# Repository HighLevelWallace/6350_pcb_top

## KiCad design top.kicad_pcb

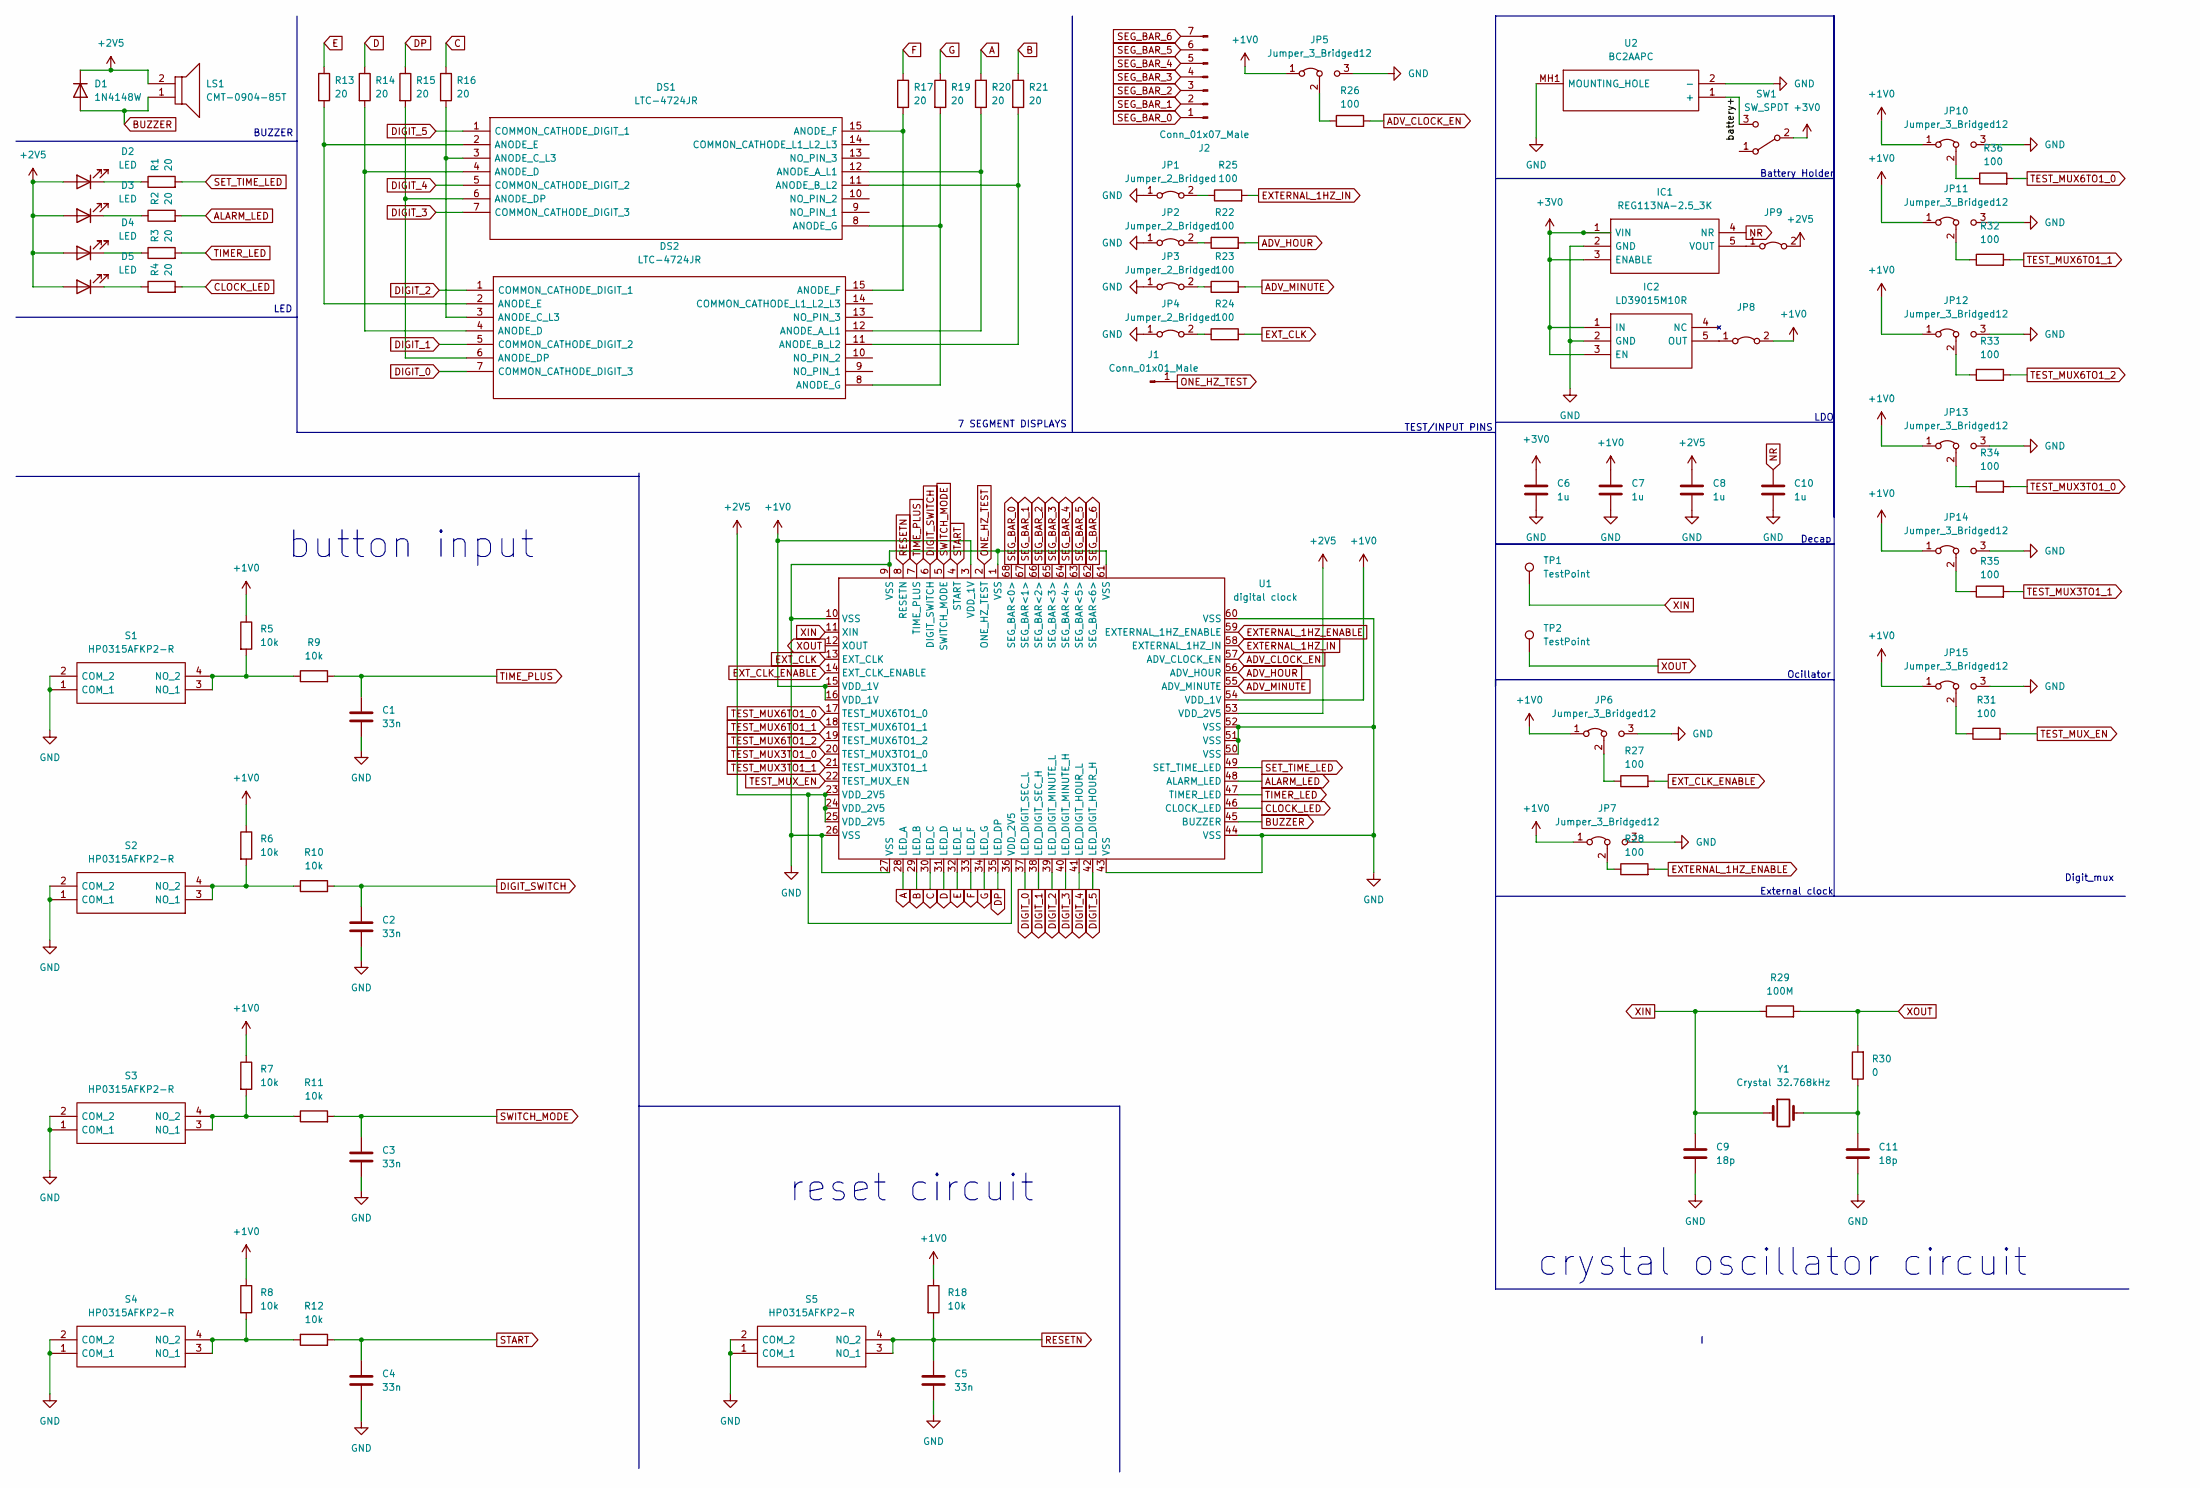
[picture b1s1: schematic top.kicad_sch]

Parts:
C1, C2, C3, C4, C5: 33n; C_1206_3216Metric_Pad1.33x1.80mm_HandSolder
C6, C7, C8, C10: 1u; C_1206_3216Metric_Pad1.33x1.80mm_HandSolder
C9, C11: 18p; C_1206_3216Metric_Pad1.33x1.80mm_HandSolder
D1: 1N4148W; D_SOD-123
D2, D3, D4, D5: LED; LED_0603_1608Metric_Pad1.05x0.95mm_HandSolder
DS1, DS2: LTC-4724JR; LTC4724JR; Manufacturer_Part_Number LTC-4724JR; Mouser Part Number 859-LTC-4724JR
IC1: REG113NA-2.5_3K; SOT95P280X145-5N; Manufacturer_Part_Number REG113NA-2.5/3K; Mouser Part Number 595-REG113NA-2.5/3K
IC2: LD39015M10R; SOT95P280X145-5N; Manufacturer_Part_Number LD39015M10R; Mouser Part Number 511-LD39015M10R
J1: Conn_01x01_Male; PinHeader_1x01_P2.54mm_Vertical
J2: Conn_01x07_Male; PinHeader_1x07_P2.54mm_Vertical
JP1, JP2, JP3, JP4, JP8, JP9: Jumper_2_Bridged; PinHeader_1x02_P2.54mm_Vertical
JP5, JP6, JP7, JP10, JP11, JP12, JP13, JP14, JP15: Jumper_3_Bridged12; PinHeader_1x03_P2.54mm_Vertical
LS1: CMT-0904-85T; CMT090485T; Manufacturer_Part_Number CMT-0904-85T; Mouser Part Number 490-CMT-0904-85T
R1, R2, R3, R4, R13, R14, R15, R16, R17, R19, R20, R21: 20; R_0603_1608Metric_Pad0.98x0.95mm_HandSolder
R5, R6, R7, R8, R9, R10, R11, R12, R18: 10k; R_1206_3216Metric_Pad1.30x1.75mm_HandSolder
R22, R23, R24, R25, R26, R27, R28, R31, R32, R33, R34, R35, R36: 100; R_1206_3216Metric_Pad1.30x1.75mm_HandSolder
R29: 100M; R_1206_3216Metric_Pad1.30x1.75mm_HandSolder
R30: 0; R_1206_3216Metric_Pad1.30x1.75mm_HandSolder
S1, S2, S3, S4, S5: HP0315AFKP2-R; HP0315AFKP2R; Manufacturer_Part_Number HP0315AFKP2-R; Mouser Part Number 633-HP0315AFKP2-R
SW1: SW_SPDT; SS-12D07-VG
TP1, TP2: TestPoint; PinHeader_1x01_P2.54mm_Vertical
U1: digital clock; PLCC68
U2: BC2AAPC; BatteryHolder_MPD_BC2AAPC_2xAA; Manufacturer_Part_Number BC2AAPC
Y1: Crystal 32.768kHz; CC5VT1A

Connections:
+1V0: C7.1, JP5.1 (A), JP6.1 (A), JP7.1 (A), JP8.2 (B), JP10.1 (A), JP11.1 (A), JP12.1 (A), JP13.1 (A), JP14.1 (A), JP15.1 (A), R5.1, R6.1, R7.1, R8.1, R18.1, U1.3 (VDD_1V), U1.15 (VDD_1V), U1.16 (VDD_1V), U1.54 (VDD_1V)
+2V5: C8.1, D1.1 (K), D2.2 (A), D3.2 (A), D4.2 (A), D5.2 (A), JP9.2 (B), LS1.2, U1.23 (VDD_2V5), U1.24 (VDD_2V5), U1.25 (VDD_2V5), U1.36 (VDD_2V5), U1.53 (VDD_2V5)
+3V0: C6.1, IC1.1 (VIN), IC1.3 (ENABLE), IC2.1 (IN), IC2.3 (EN), SW1.2 (B)
A: R20.1, U1.28 (LED_A)
ADV_CLOCK_EN: R26.2, U1.57 (ADV_CLOCK_EN)
ADV_HOUR: R22.2, U1.56 (ADV_HOUR)
ADV_MINUTE: R23.2, U1.55 (ADV_MINUTE)
ALARM_LED: R2.2, U1.48 (ALARM_LED)
B: R21.1, U1.29 (LED_B)
BUZZER: D1.2 (A), LS1.1, U1.45 (BUZZER)
C: R16.1, U1.30 (LED_C)
CLOCK_LED: R4.2, U1.46 (CLOCK_LED)
D: R14.1, U1.31 (LED_D)
DIGIT_0: DS2.7 (COMMON_CATHODE_DIGIT_3), U1.37 (LED_DIGIT_SEC_L)
DIGIT_1: DS2.5 (COMMON_CATHODE_DIGIT_2), U1.38 (LED_DIGIT_SEC_H)
DIGIT_2: DS2.1 (COMMON_CATHODE_DIGIT_1), U1.39 (LED_DIGIT_MINUTE_L)
DIGIT_3: DS1.7 (COMMON_CATHODE_DIGIT_3), U1.40 (LED_DIGIT_MINUTE_H)
DIGIT_4: DS1.5 (COMMON_CATHODE_DIGIT_2), U1.41 (LED_DIGIT_HOUR_L)
DIGIT_5: DS1.1 (COMMON_CATHODE_DIGIT_1), U1.42 (LED_DIGIT_HOUR_H)
DIGIT_SWITCH: C2.1, R10.2, U1.6 (DIGIT_SWITCH)
DP: R15.1, U1.35 (LED_DP)
E: R13.1, U1.32 (LED_E)
EXTERNAL_1HZ_ENABLE: R28.2, U1.59 (EXTERNAL_1HZ_ENABLE)
EXTERNAL_1HZ_IN: R25.2, U1.58 (EXTERNAL_1HZ_IN)
EXT_CLK: R24.2, U1.13 (EXT_CLK)
EXT_CLK_ENABLE: R27.2, U1.14 (EXT_CLK_ENABLE)
F: R17.1, U1.33 (LED_F)
G: R19.1, U1.34 (LED_G)
GND: C1.2, C2.2, C3.2, C4.2, C5.2, C6.2, C7.2, C8.2, C9.2, C10.2, C11.2, IC1.2 (GND), IC2.2 (GND), JP1.1 (A), JP2.1 (A), JP3.1 (A), JP4.1 (A), JP5.3 (B), JP6.3 (B), JP7.3 (B), JP10.3 (B), JP11.3 (B), JP12.3 (B), JP13.3 (B), JP14.3 (B), JP15.3 (B), S1.1 (COM_1), S1.2 (COM_2), S2.1 (COM_1), S2.2 (COM_2), S3.1 (COM_1), S3.2 (COM_2), S4.1 (COM_1), S4.2 (COM_2), S5.1 (COM_1), S5.2 (COM_2), SW1.4, SW1.5, U1.1 (VSS), U1.9 (VSS), U1.10 (VSS), U1.26 (VSS), U1.27 (VSS), U1.43 (VSS), U1.44 (VSS), U1.50 (VSS), U1.51 (VSS), U1.52 (VSS), U1.60 (VSS), U1.61 (VSS), U2.2 (-), U2.MH1 (MOUNTING_HOLE)
NR: C10.1, IC1.4 (NR)
unnamed: C11.1, R30.1, Y1.2
unnamed: D2.1 (K), R1.1
unnamed: D3.1 (K), R2.1
unnamed: D4.1 (K), R3.1
unnamed: D5.1 (K), R4.1
unnamed: DS1.2 (ANODE_E), DS2.2 (ANODE_E), R13.2
unnamed: DS1.3 (ANODE_C_L3), DS2.3 (ANODE_C_L3), R16.2
unnamed: DS1.4 (ANODE_D), DS2.4 (ANODE_D), R14.2
unnamed: DS1.6 (ANODE_DP), DS2.6 (ANODE_DP), R15.2
unnamed: DS1.8 (ANODE_G), DS2.8 (ANODE_G), R19.2
unnamed: DS1.11 (ANODE_B_L2), DS2.11 (ANODE_B_L2), R21.2
unnamed: DS1.12 (ANODE_A_L1), DS2.12 (ANODE_A_L1), R20.2
unnamed: DS1.15 (ANODE_F), DS2.15 (ANODE_F), R17.2
unnamed: IC1.5 (VOUT), JP9.1 (A)
unnamed: IC2.5 (OUT), JP8.1 (A)
unnamed: JP1.2 (B), R25.1
unnamed: JP2.2 (B), R22.1
unnamed: JP3.2 (B), R23.1
unnamed: JP4.2 (B), R24.1
unnamed: JP5.2 (C), R26.1
unnamed: JP6.2 (C), R27.1
unnamed: JP7.2 (C), R28.1
unnamed: JP10.2 (C), R36.1
unnamed: JP11.2 (C), R32.1
unnamed: JP12.2 (C), R33.1
unnamed: JP13.2 (C), R34.1
unnamed: JP14.2 (C), R35.1
unnamed: JP15.2 (C), R31.1
unnamed: R5.2, R9.1, S1.3 (NO_1), S1.4 (NO_2)
unnamed: R6.2, R10.1, S2.3 (NO_1), S2.4 (NO_2)
unnamed: R7.2, R11.1, S3.3 (NO_1), S3.4 (NO_2)
unnamed: R8.2, R12.1, S4.3 (NO_1), S4.4 (NO_2)
unnamed: SW1.3 (C), U2.1 (+)
ONE_HZ_TEST: J1.1, U1.2 (ONE_HZ_TEST)
RESETN: C5.1, R18.2, S5.3 (NO_1), S5.4 (NO_2), U1.8 (RESETN)
SEG_BAR_0: J2.1, U1.68 (SEG_BAR<0>)
SEG_BAR_1: J2.2, U1.67 (SEG_BAR<1>)
SEG_BAR_2: J2.3, U1.66 (SEG_BAR<2>)
SEG_BAR_3: J2.4, U1.65 (SEG_BAR<3>)
SEG_BAR_4: J2.5, U1.64 (SEG_BAR<4>)
SEG_BAR_5: J2.6, U1.63 (SEG_BAR<5>)
SEG_BAR_6: J2.7, U1.62 (SEG_BAR<6>)
SET_TIME_LED: R1.2, U1.49 (SET_TIME_LED)
START: C4.1, R12.2, U1.4 (START)
SWITCH_MODE: C3.1, R11.2, U1.5 (SWITCH_MODE)
TEST_MUX3TO1_0: R34.2, U1.20 (TEST_MUX3TO1_0)
TEST_MUX3TO1_1: R35.2, U1.21 (TEST_MUX3TO1_1)
TEST_MUX6TO1_0: R36.2, U1.17 (TEST_MUX6TO1_0)
TEST_MUX6TO1_1: R32.2, U1.18 (TEST_MUX6TO1_1)
TEST_MUX6TO1_2: R33.2, U1.19 (TEST_MUX6TO1_2)
TEST_MUX_EN: R31.2, U1.22 (TEST_MUX_EN)
TIMER_LED: R3.2, U1.47 (TIMER_LED)
TIME_PLUS: C1.1, R9.2, U1.7 (TIME_PLUS)
XIN: C9.1, R29.1, TP1.1, U1.11 (XIN), Y1.1
XOUT: R29.2, R30.2, TP2.1, U1.12 (XOUT)

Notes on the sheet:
External clock
TEST/INPUT PINS
button input
BUZZER
Decap
crystal oscillator circuit
Ocillator
7 SEGMENT DISPLAYS
LDO
reset circuit
Battery Holder
LED
Digit_mux

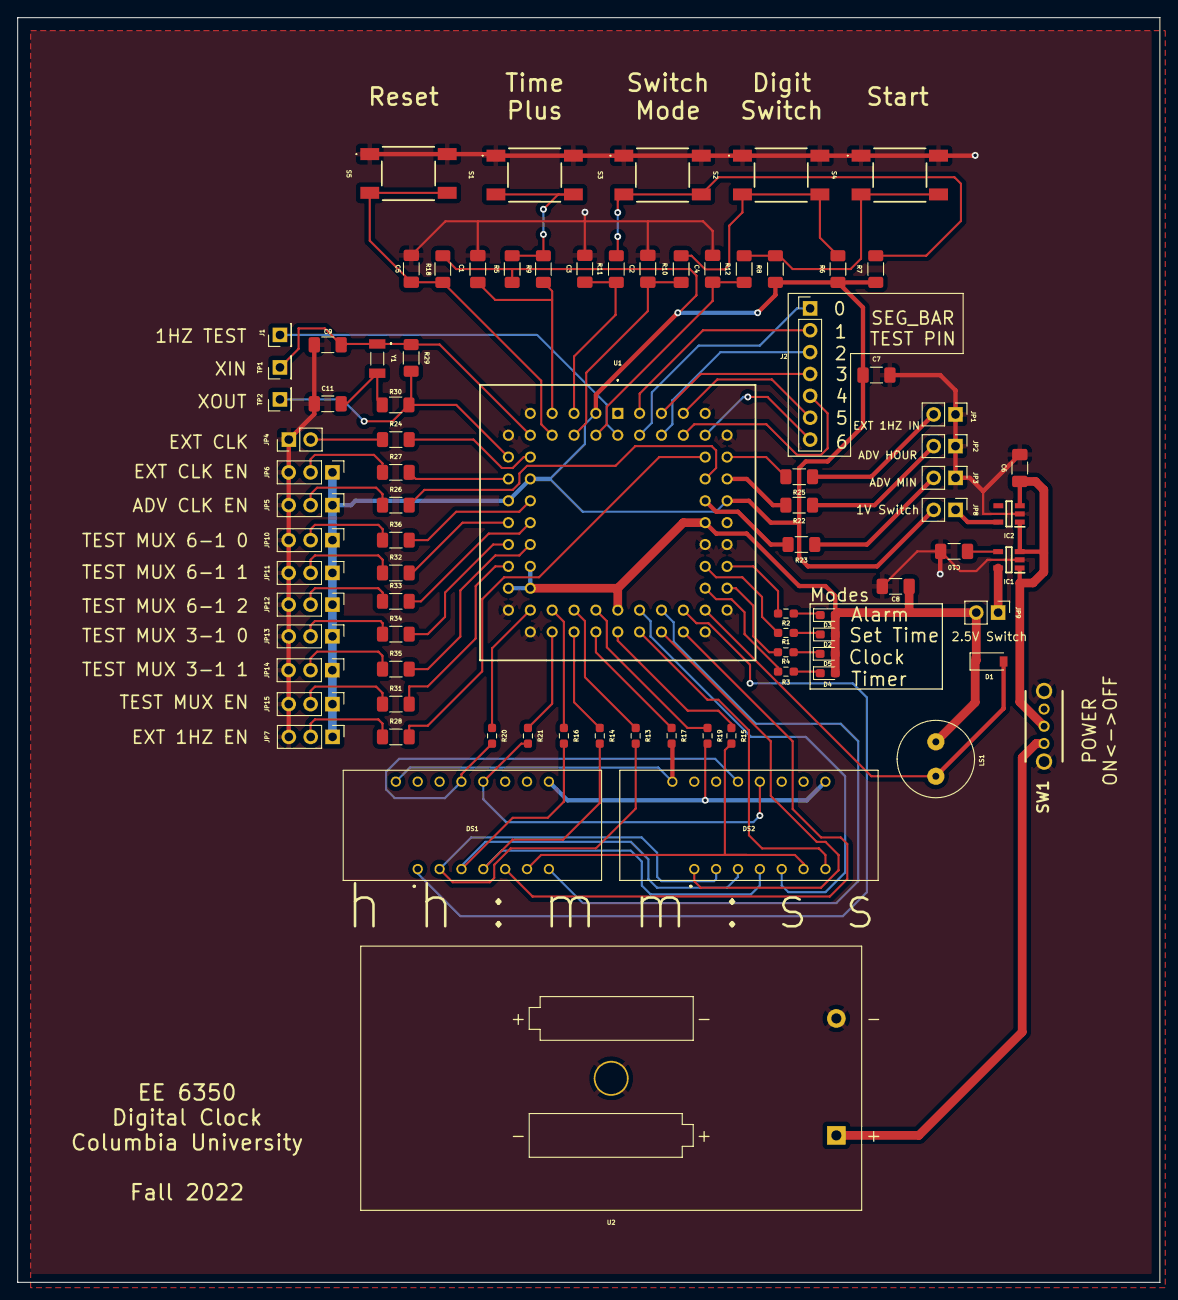
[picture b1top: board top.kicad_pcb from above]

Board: 2 copper layers, 132.7 x 146.9 mm, 85 parts (0 on the bottom side), 85 nets.

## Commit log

2022-09-23 Placement done
2022-09-23 Placement done. Require routing
2022-09-26 Final
